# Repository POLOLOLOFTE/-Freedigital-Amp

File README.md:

# -Freedigital-Amp

a full analogic amplificator 2.1, built around tda2030. very Open Source!!! so everyone can make it like they want!!
For Half Life (Hackclub)

i have do it because i love music and i got some "great" speakers recycled from the trash, and i would rather make my own amplificator than let some multibilionare company do it for me and not get the best... btw i don't think that mine is better than some product made from years of reserch. but it's my amp! and all the work that i put it on it's all worth it!

the audio from a standard jack comes in and it goes trough some componets to introduce it to 3 tda2030 (the main amplificator process) they are three so one is for the right signal one if for the left and the third is for the subwoofer.
it's designed on a small foarm 100x100mm custom pcb and the tda2030 need passive cooling even if they have a thermal shut down emergency mode.
(the wireing digramm is nota thing to explain on a simple text(it's harder with my broken english) so this is how i'm going to explain it, sorry)

## INPUT:
it work with one jack from a phone/computer and 16 volt from a powersupply aon 3-4 amps.

## OUTPUT:
there are three screw clamp (other than the audio) or spring clamp on the rear where you put the positive and negative of the speakers... remember the speakers shouldn't more than 50w 8ohms each

## SETTINGS:
there are three potenziometers for each tda2030 so you can control endidually the left, right and subwoofer audio

### Extra Note:
The pcb isn'perfect there can be some static noise from the circuit and it's not made for staying 24/7 powered at 100% of volume

## Assembly
as materials you need what is in the bom on the bottom on the readme:

- you have to soder on the pcb all the components(you need soder and a iron); whaching the schematic(at the end of the readme)
- then you are good to go! just power the board from the screw connector neat the jack
- hook up some speakers and a subwoofer(opsional)
- put in the jack (from a phone/computer)
- enjoy the music

 # **IMPORTANT**

 ** The pcb is UNTESTED so it can blew up for something wrong do NOT fully thrust the system so much,
 I am NOT rensponsible if it blow up CAPACITORS ot TDA2030s **

| Item Name | Qty | Price (total) (USD) | Item link | Notes |
| --- | --- | --- | --- | --- |
| TDA2030 | 3 | $6.69 | https://www.amazon.it/-/en/gp/product/B07CJY4255/ref=ox_sc_act_title_8?smid=AXQNTRGL896M5&psc=1 | The main chip |
| 1N4001 | 6 | $8.96 | https://www.amazon.it/AUKENIEN-Pieces-Rectifier-Electronic-Silicone/dp/B08Y8KLFWW/ref=sxin_10_pa_sp_search_thematic_sspa?content-id=amzn1.sym.f05bb22c-b10e-43e7-b840-674903c7db32%3Aamzn1.sym.f05bb22c-b10e-43e7-b840-674903c7db32&crid=2FYDE8PDXCJSS&cv_ct_cx=1n4001&keywords=1n4001&pd_rd_i=B08Y8KLFWW&pd_rd_r=f538e61c-1c49-43fd-99dc-07afb98a1078&pd_rd_w=2Y1jS&pd_rd_wg=5yTNH&pf_rd_p=f05bb22c-b10e-43e7-b840-674903c7db32&pf_rd_r=GJRGVC585KR0FBXZC48R&qid=1792769780&sbo=RZvfv%2F%2FHxDF%2BO5021pAnSA%3D%3D&sprefix=1n4001%2Caps%2C182&sr=1-2-50840d04-82cc-4adf-b6cc-9f330c77868e-spons&aref=z7QERglYFX&sp_csd=d2lkZ2V0TmFtZT1zcF9zZWFyY2hfdGhlbWF0aWM&psc=1 | you can get 200 for 9 dollars |
| resistor 10k | 2 | $15.69 | https://www.amazon.it/-/en/gp/product/B0FP51H3ML/ref=ox_sc_act_title_1?smid=A2X2IS1I8BHRL9&psc=1 | you can get all of them once |
| resistor 100k | 6 | | | get this in a kit |
| resistor 22k | 3 | | | get this in a kit |
| resistor 680Ω | 3 | | | get this in a kit |
| resistor 1Ω | 3 | | | get this in a kit |
| resistor 10Ω 5W | 1 | $16.25 | https://www.amazon.it/-/en/Innfeeltech-Tolerance-Resistor-Projects-Experiments/dp/B0FG25S9BR/ref=sr_1_7?crid=1B0NPLK2B32TC&dib=eyJ2IjoiMSJ9.Scs8-FuewxLpGOpdGYz0p2tV7cUOCUX3GF4mUKxI1DU6NA7-bN_V4clB0l8TXbvCzyKTaMt7hNnqy144VDAkcVWwwOL5zHRgJeIZP5KMo7o2mDFh1wKYmf8kLG0Ex5gra7KmvPm2B27ffWNTpQ7EHBUOGSfsWj7aaAMh_Ib9G6LY1fFMWFBnrSwezEhFxQ-VS8OXPOCDQgXI3IvHK9Ex_7MSvVvFpufJz9n3aWbGZEp9M5V6lziDasb1AsIVlXLdFRg1TSwQ5UKuXucKiTjfUnr0hortJ1ijx7xrTfaXo9w.l0t8KEW1TYORQRVuwqhuOfhoq3YdMGw8-xbfqjIcLOk&dib_tag=se&keywords=10homs+5w+resistor&qid=1792770093&s=industrial&sprefix=10homs+5w+resisto%2Cindustrial%2C120&sr=1-7 | the ceramic one |
| copper wire 0.8-1mm | 10-12 turns | $14.57 | https://www.amazon.it/-/en/gp/product/B0CS8V42H3/ref=ox_sc_act_title_6?smid=A1LK21T5CK0Y8M&psc=1 | to wrap it around the ceramic resistor |
| condensator 10uf 25V | 3 | $7.29 | https://www.amazon.it/-/en/Aluminum-Electrolytic-Capacitor-25V-Microwave/dp/B0FDPWGWWJ/ref=sr_1_9?crid=C5BOM4U6KYXF&dib=eyJ2IjoiMSJ9.LSiuYq2FCh0egSiZCVXBDgtqf9YRCTDODsGoj1gyV6TElrz6s4esagkWBgiefzRJAuGFnkvvwxGyJs2YDObtWuDjz7T60MvbGR_hxPi1jN4JcUpgRRN37HkW_qJ7sHODQNGvibzaGK_W4DFvwFPmyR_azW77qsArORLo2YgN_yHKFh-rWc43EsYec8otTvvkiasBQ4wfymVjEPNe2Xu7K-jK0HUUxnrVwYNTO_mvWvFf-mO4lEYdYTu0oAr5MqE4Ytclr2J4mcEDzkZXTj1AB3bC-yykBzvX1E1-0aRBpWY.zjHfs2OkTKXnMhnPGOdG_Vhhd5duc5kQ1GFVzTE5KIA&dib_tag=se&keywords=condensatore+10uf+25v&qid=1792770669&s=industrial&sprefix=condensatore+10uf+25v%2Cindustrial%2C126&sr=1-9 | |
| condensator 22uf 25V | 3 | $8.30 | https://www.amazon.it/-/en/QUARKZMAN-Electrolytic-Capacitor-Aluminium-Capacitors/dp/B0G56FWVGX/ref=sr_1_4?crid=T98MPAVDTA2Z&dib=eyJ2IjoiMSJ9.L_odFOx6XBQYejsZhqHLbnYJxT4VA790aNziTO0ag_o-CVstSlUV35lNNkYwe-fO3bMDnziuRYyJuWM2jBvAMqZUBNnOFOOESn_EPpkrTYIA09VNIGPmrbc94JB8liU2UyafeMaqphUhBk9qcQLDEmi-FqVWOQuaHnjy-VhnsRfsSmXaV4dCGTpwh7yIWWF5B4fav4ixdl-6k6JYpeGj6UAGbZV6O4xUirx0J722WVyTDwP4kWF-R-4ltd0emhUx1L3Eio61yE1LcZXQkPZDR4xFHuVjhCGLoxXnODxKEfU.3vi3UqI9uoCa8QOpzKgGD75RI-VM42V7wuLpVwEScnM&dib_tag=se&keywords=condensatore+22uf+25v&qid=1792770738&s=industrial&sprefix=condensatore+22uf+25v%2Cindustrial%2C115&sr=1-4 | |
| condensator 2200uf 25V | 4 | $8.54 | https://amazon.it | |
| condensator 100nf | 6 | $11.13 | https://www.amazon.it/-/en/Multilayer-Monolithic-Capacitors-Different-Electronic/dp/B0GWMVTD1H/ref=sr_1_10?crid=2IVX3RRIZURSU&dib=eyJ2IjoiMSJ9.n1xKTGmbGyA-2SUZmJkTlhj1pfeyEPUzMORMi8h4CCsmk1a1i4k1xN8dUSgnCa3tQPm358qEAAEQ15NSxepj8qwEqLJszSWEWAr8j5-X6zElzeAEmQn1wj4tCrYmazUmn8kNuconuhvtxebJ3uRPUeMi3Bpui8cRIXso5xAqH3-Zg78oxSXLCUVnQsAxmTLCFKPjzCgq9VVdLLTMSbLgNN2Nr9kvSZdmANI6LPrSGo6t628Emrm6LWSAnCX1pR8c32nfPsRIbP8kALbTqat1lqTiQ1UdbWS1oLH6qRDOOlU.RXlpA9rYWzoFDd-YUg6GLDR6kHqAqU8k40__FQYSrNg&dib_tag=se&keywords=condensatore+104&qid=1792770951&s=industrial&sprefix=condensatore+104%2Cindustrial%2C124&sr=1-10 | |
| condensator 220nf | 3 | $16.82 | https://www.amazon.it/CBB81-1000V-Polypropylene-Capacitor-Voltage/dp/B0DCFXJFJM/ref=sr_1_13_sspa?crid=3J1ZVXC4BB3I7&dib=eyJ2IjoiMSJ9.jo-a6Ciacp2sMADAmsIOFcdenbnVn-4VdGcrCjea3hOtvWWpXNY71hP0WcLw4umcaz2ZxhqXUrmedS1rc9FUGeao73UcibcFCBHOvopEnppHOCEWVuT6uCkoiccAhFUC5-rhIIr4KjcS7k_ZlzaBkVn9vCaSdD0OP4urf7HGmUHy9SY-ymL3IKlmf9onsAbCTgWG7RwChiAQ6LVTx0HpcHZp8Yf9NLepB1lkEjijMY70AITAFYhDGnwkSJH6Nl3fhYweobUhyw8oSV44EQe9gTrR_KR4KuGUR_DbNE-mTJM.2CRdwFxtc0T46XKF9F-Ga5nRPtz1mBHe0kxWrt8LJio&dib_tag=se&keywords=condensatore+220nf&qid=1792771250&s=industrial&sprefix=condensatore+220nf%2Cindustrial%2C125&sr=1-13-spons&aref=tX19d3y0Os&sp_csd=d2lkZ2V0TmFtZT1zcF9tdGY&psc=1 | |
| 10k potenziometer | 3 | $11.20 | https://www.amazon.it/-/en/RUNCCI-YUN-Terminal-Rotary-Potentiometer-Linear/dp/B07RHJZ979/ref=sr_1_7?crid=21ICWWCGYB47L&dib=eyJ2IjoiMSJ9.CiF77j-BQNJ4ELBIJbrLTxFxpHBgf2ZDOHHu2dMKAQv_OqEwOZhciXMFus_fFrV6MJJrFIxIJzSyazEZtxOnNPYMBW44sJYdX5zu6exgKgplnSsKDzo9yYdNiAP2LPL3VNkwpEUikDPUvRI-s46rGfOx3ksRKzOsUKgzUfTjY8pA0sGaYYu5HWuNkid3oSmawHv867Y1tGr24BIbT3NmuhNl56rc0qJZ4AxU618JSVTm_Ikm11hWA39cMWUDXyympY6SD8PKnhr9aBR3rqEe1HDKibaygzQ4RiVotVpDtjI.CWnLL06XeDyoejRoiuHzGrOZsavvX4bzLuTi4I2dUkY&dib_tag=se&keywords=10k%2Bpotentiometer&qid=1792771074&sprefix=10k%2Bpotentiometer%2Caps%2C157&sr=8-7&th=1 | |
| one 3.5mm jack input | 1 | $8.86 | https://www.amazon.it/-/en/3-5mm-Female-Stereo-Jack-Disconnect/dp/B0868TM4FC/ref=sr_1_18?crid=3CDLKFXA0JAAQ&dib=eyJ2IjoiMSJ9.wjOHOwoahBhJfJiL1YiRXxd8mS7PK7O5BqYpGmYIO_Ry6CkByLdsht2toxIKSCyUu8hlNAH8Vjbdxk2XPODj5tYiMD70uTLDZQkX8fYuzc3jXrxdIbplqkGgnuuV5B_uSlYVPkaNkTVNM5Y6b74yvfiF5JZ67hNufQDMiOFBL3WNoFw2yBZZGTlsuKwYb8HylG8KO7wmFy2sJZKNmsJuE0rwiZAftr_7XPnEx77ET6UZWcqcy7xm-SbJbFKj-8UVqA1F9sVHBKWREKkzrTjUUVrLG3uTcVi_JwmZA5EbSBM.rp3jBQOJ1NRV5HjDUlxTJFbqKY1S91YfKkDw7e8B85Y&dib_tag=se&keywords=jack+input+3.5mm+pcb&qid=1792785978&sprefix=jack+input+3.5mm+pcb%2Caps%2C125&sr=8-18 | the wide one |
| set of 1x2/1x3 screw terminals | 6 | $12.33 | https://www.amazon.it/-/en/gp/product/B0FN6VYSFN/ref=ox_sc_act_title_4?smid=A2KWOEY1RHRC64&psc=1 | you can use other tipe of compatible connector |
| the pcb itself | 1 | $4.00 | | the cost depends a lot |
| heat sink | 3 | $8.96 | https://www.amazon.it/gp/product/B0CSJVJ4CG/ref=ox_sc_act_title_3?smid=A2FXWI8CY4G34J&psc=1 | |
| Total Price (USD): | | $159.59 | | |

## here is the list for pcb <-> components so you don't just guess😁👍:

- [ ] U1, U2, U3		TDA2030	
  
- [ ] D1–D6		1N4001	(they are 6 and you can put similar diods in it)
  
- [ ] R1, R2		10k	sub low-pass filter

- [ ] R4, R5, R6, R7, R18, R19		100k	8V bias divider

- [ ] R14, R15, R16		22k	feedback

- [ ] R8, R9, R10		680Ω	pin 2 network

- [ ] R11, R12, R13		1Ω	output stability network

- [ ] R17		10Ω 5W	in parallel with L1

- [ ] L1  	1–2µH	turns wound on R17
 (for cost reason thoose two are thogheter... like you connect the resistor and then you run 10-12 spirals of copper wire)

- [ ] C1, C2, C3		10µF 25V	input coupling

- [ ] C5, C7, C8		22µF 25V	pin 2 network

- [ ] C4, C15, C16		2200µF 25V	output coupling

- [ ] C6	1	2200µF 25V	power supply reservoir

- [ ] C9, C10, C11		100nF	output stability network

- [ ] C12, C13, C14		100nF	supply decoupling at pin 5

- [ ] C17		220nF	sub filter

- [ ] RV1, RV2, RV3		10k potentiometer	volume-for each speaker

- [ ] J1		3.5mm audio jack	input

- [ ] J2, J3, J4		2-pin terminal block speakers

- [ ] J5		2-pin terminal block	16V power input

- [ ] J6		5-pin terminal block	test points

- [ ] then you need the custom pcb: you find it in the extra folder

- [ ] speakers 2 standard and 1 subwoofer: !MAX! 4ohms 50w

- [ ] and you probably need some heat sink: werever you have to stay cheap

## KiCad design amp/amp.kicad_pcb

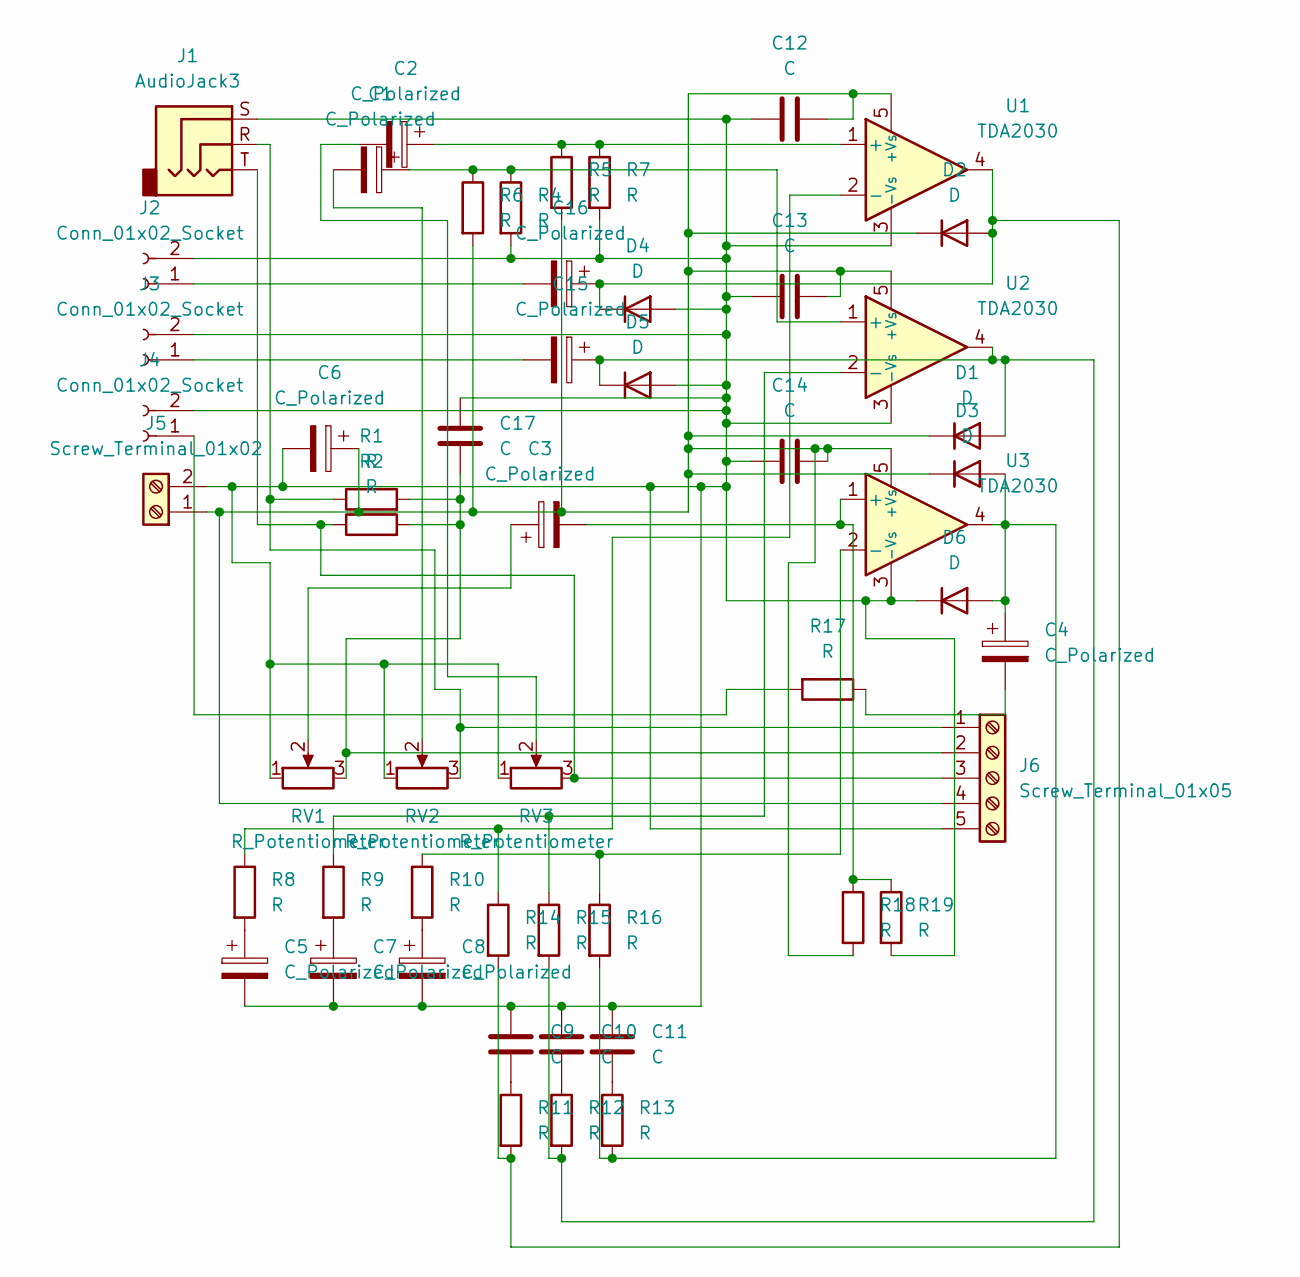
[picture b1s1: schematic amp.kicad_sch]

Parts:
C1, C2, C3, C5, C7, C8: C_Polarized; CP_Radial_D6.3mm_P2.50mm
C4, C6, C15, C16: C_Polarized; CP_Radial_D12.5mm_P5.00mm
C9, C10, C11, C12, C13, C14, C17: C; C_Disc_D4.7mm_W2.5mm_P5.00mm
D1, D2, D3, D4, D5, D6: D; D_DO-41_SOD81_P10.16mm_Horizontal
J1: AudioJack3; Jack_3.5mm_CUI_SJ1-3523N_Horizontal
J2, J3, J4: Conn_01x02_Socket; TerminalBlock_MetzConnect_Type055_RT01502HDWU_1x02_P5.00mm_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
J5: Screw_Terminal_01x02; TerminalBlock_Phoenix_MKDS-1,5-2_1x02_P5.00mm_Horizontal
J6: Screw_Terminal_01x05; TerminalBlock_Phoenix_MKDS-1,5-5_1x05_P5.00mm_Horizontal
R1, R2, R4, R5, R6, R7, R8, R9, R10, R11, R12, R13, R14, R15, R16, R18, R19: R; R_Axial_DIN0207_L6.3mm_D2.5mm_P7.62mm_Horizontal
R17: R; R_Axial_DIN0922_L20.0mm_D9.0mm_P25.40mm_Horizontal
RV1, RV2, RV3: R_Potentiometer; Potentiometer_Alps_RK09L_Single_Vertical
U1, U2, U3: TDA2030; TO-220-5_Vertical

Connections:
unnamed: C1.2, RV2.2
unnamed: C2.2, RV3.2
unnamed: C3.1, RV1.2
unnamed: C4.2, R17.1
unnamed: C5.1, R8.2
unnamed: C7.1, R9.2
unnamed: C8.1, R10.2
unnamed: C9.2, R11.1
unnamed: C10.2, R12.1
unnamed: C11.2, R13.1
unnamed: C15.1, D1.2 (A), D5.1 (K), R12.2, R15.2, U2.4
unnamed: C6.1, C12.2, C13.2, C14.2, D1.1 (K), D2.1 (K), D3.1 (K), J5.1, J6.4, R5.2, R6.2, R18.2, U1.5 (+Vs), U2.5 (+Vs), U3.5 (+Vs)
unnamed: C16.1, D2.2 (A), D4.1 (K), R11.2, R14.2, U1.4
unnamed: C4.1, D3.2 (A), D6.2 (A), R13.2, R16.2, U3.4
unnamed: C5.2, C6.2, C7.2, C8.2, C9.1, C10.1, C11.1, C12.1, C13.1, C14.1, C17.1, D4.2 (A), D5.2 (A), D6.1 (K), J1.S, J2.2, J3.2, J4.2, J5.2, J6.5, R4.2, R7.2, R19.2, RV1.1, RV2.1, RV3.1, U1.3 (-Vs), U2.3 (-Vs), U3.3 (-Vs)
unnamed: C16.2, J2.1
unnamed: C15.2, J3.1
unnamed: J4.1, R17.2
unnamed: J1.R, J6.1, R1.1, RV2.3
unnamed: C17.2, J6.2, R1.2, R2.2, RV1.3
unnamed: J1.T, J6.3, R2.1, RV3.3
unnamed: C2.1, R5.1, R7.1, U1.1 (+)
unnamed: R8.1, R14.1, U1.2 (-)
unnamed: C1.1, R4.1, R6.1, U2.1 (+)
unnamed: R9.1, R15.1, U2.2 (-)
unnamed: C3.2, R18.1, R19.1, U3.1 (+)
unnamed: R10.1, R16.1, U3.2 (-)

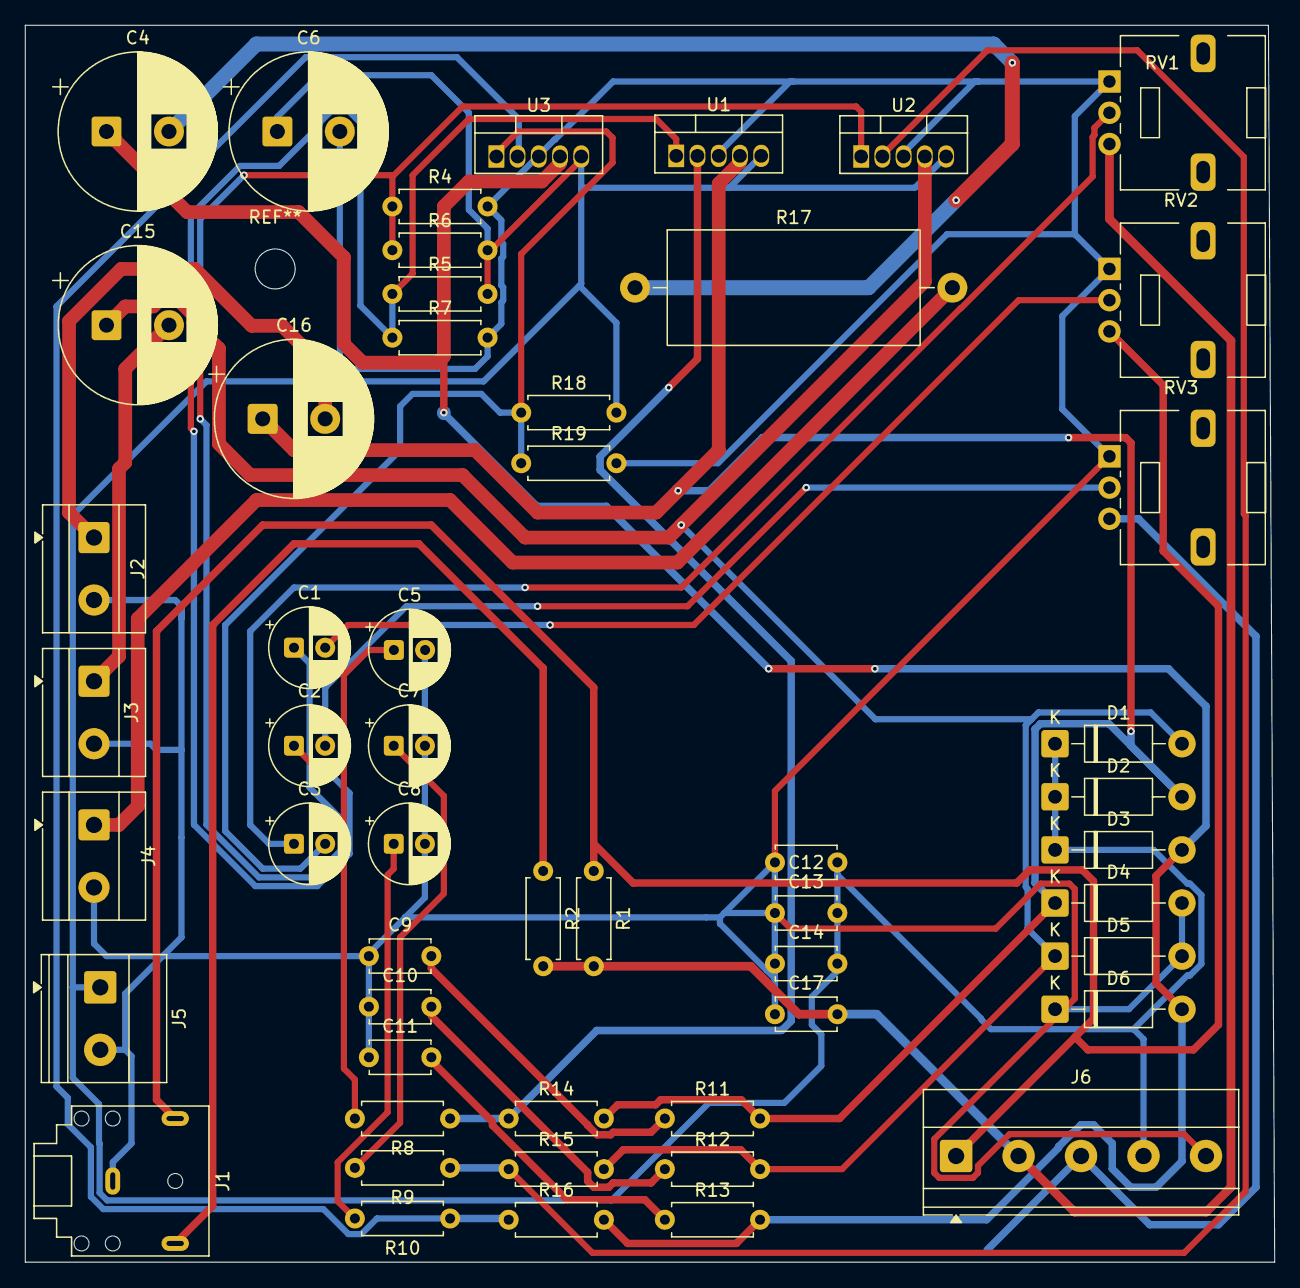
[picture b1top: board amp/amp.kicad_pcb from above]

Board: 2 copper layers, 100.0 x 99.0 mm, 53 parts (0 on the bottom side), 27 nets.

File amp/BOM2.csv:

This is the material that you accually need to make it:

U1, U2, U3	3	TDA2030	
  
D1–D6	6	1N4001	
  
R1, R2	2	10k	sub low-pass filter
R4, R5, R6, R7, R18, R19	6	100k	8V bias divider
R14, R15, R16	3	22k	feedback
R8, R9, R10	3	680Ω	pin 2 network
R11, R12, R13	3	1Ω	output stability network
R17	1	10Ω 5W	in parallel with L1

L1	1	1–2µH	turns wound on R17

C1, C2, C3	3	10µF 25V	input coupling
C5, C7, C8	3	22µF 25V	pin 2 network
C4, C15, C16	3	2200µF 25V	output coupling
C6	1	2200µF 25V	power supply reservoir
C9, C10, C11	3	100nF	output stability network (Boucherot)
C12, C13, C14	3	100nF	supply decoupling at pin 5
C17	1	220nF	sub filter

RV1, RV2, RV3	3	10k potentiometer	volume

J1	1	3.5mm audio jack	input
J2, J3, J4	3	2-pin terminal block	speakers
J5	1	2-pin terminal block	16V power input
J6	1	5-pin terminal block	test points

then you need the custom pcb: you find it in the extra folder

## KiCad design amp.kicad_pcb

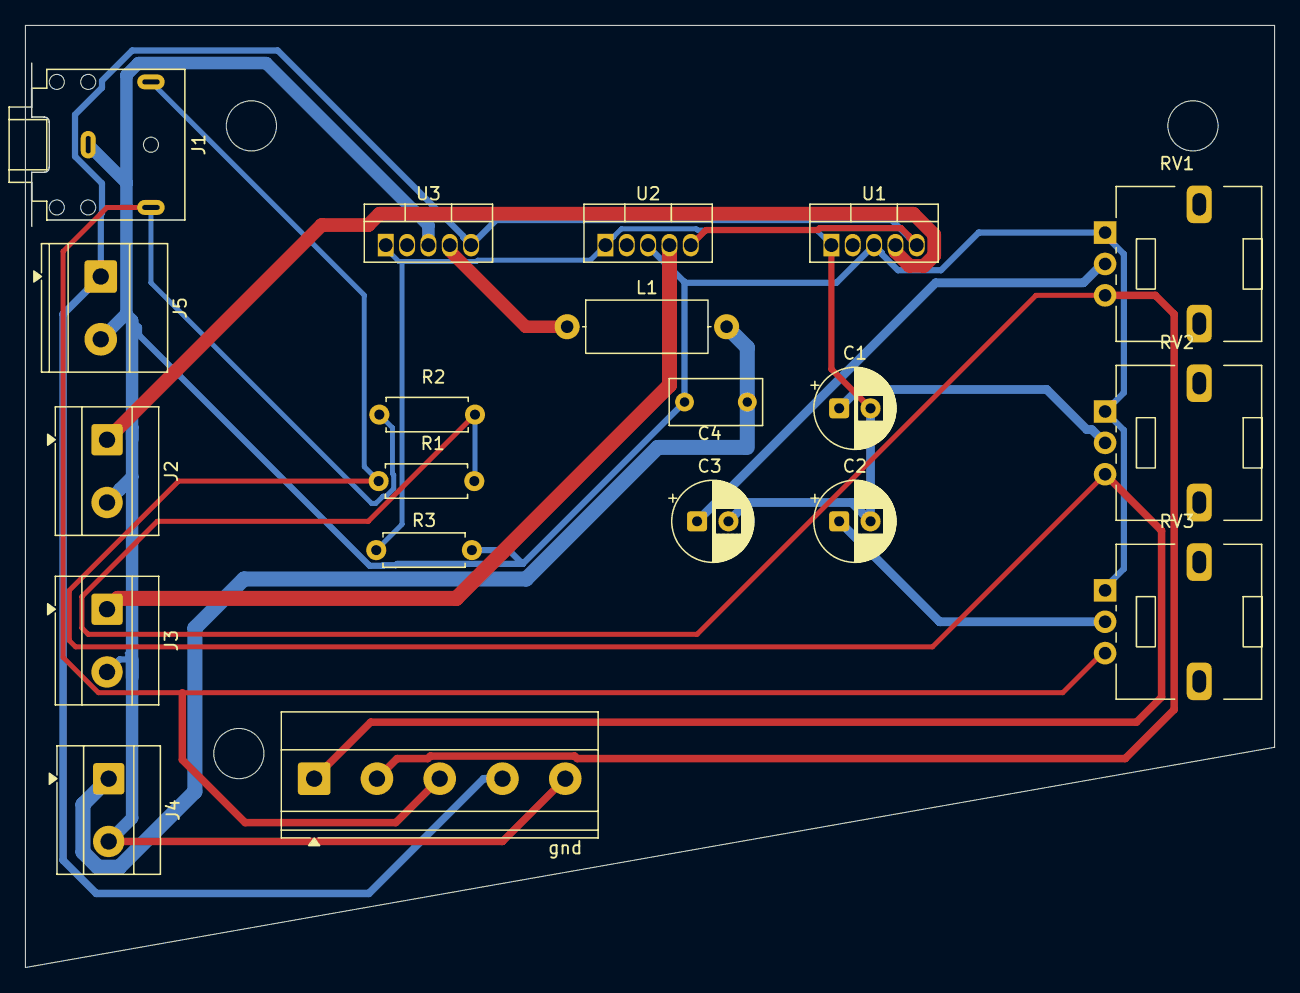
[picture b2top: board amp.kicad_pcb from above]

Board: 2 copper layers, 99.5 x 75.0 mm, 20 parts (0 on the bottom side), 13 nets.

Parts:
C1, C2, C3: C_Polarized; CP_Radial_D6.3mm_P2.50mm
C4: C; C_Rect_L7.2mm_W3.5mm_P5.00mm
J1: AudioJack3; Jack_3.5mm_CUI_SJ1-3523N_Horizontal
J2, J3: pitch; TerminalBlock_MetzConnect_Type055_RT01502HDWU_1x02_P5.00mm_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
J4: subwoofer; TerminalBlock_MetzConnect_Type055_RT01502HDWU_1x02_P5.00mm_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
J5: Screw_Terminal; TerminalBlock_Phoenix_MKDS-1,5-2_1x02_P5.00mm_Horizontal
L1: passive filter; L_Axial_L9.5mm_D4.0mm_P12.70mm_Horizontal_Fastron_SMCC
R1, R2, R3: R; R_Axial_DIN0207_L6.3mm_D2.5mm_P7.62mm_Horizontal
RV1, RV2, RV3: Potentiometer; Potentiometer_Alps_RK09L_Single_Vertical
U1, U2, U3: TDA2030; TO-220-5_Vertical
gnd: Screw_Terminal_01x05; TerminalBlock_Phoenix_MKDS-1,5-5_1x05_P5.00mm_Horizontal

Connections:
unnamed: C1.1, RV2.2
unnamed: C2.1, RV3.2
unnamed: C3.1, RV1.2
unnamed: J2.1, U1.4
unnamed: C4.1, J1.S, J2.2, J3.2, J4.2, J5.2, R3.2, RV1.1, RV2.1, RV3.1, U1.3 (-Vs), U2.3 (-Vs), U3.3 (-Vs), gnd.5
unnamed: J3.1, U2.4
unnamed: C4.2, J4.1, L1.2
unnamed: J5.1, U1.5 (+Vs), U2.5 (+Vs), U3.5 (+Vs), gnd.4
unnamed: J1.R, R1.1, RV2.3, gnd.1
unnamed: R1.2, R2.2, RV1.3, gnd.2
unnamed: J1.T, R2.1, RV3.3, gnd.3
unnamed: L1.1, U3.4
unnamed: C1.2, C2.2, C3.2, R3.1, U1.1 (+), U2.1 (+), U3.1 (+)
